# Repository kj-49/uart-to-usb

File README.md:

## UART to USB

A simple chip that converts up to 3 UART lines to USB. Only supports one-way transmission from UART to USB.

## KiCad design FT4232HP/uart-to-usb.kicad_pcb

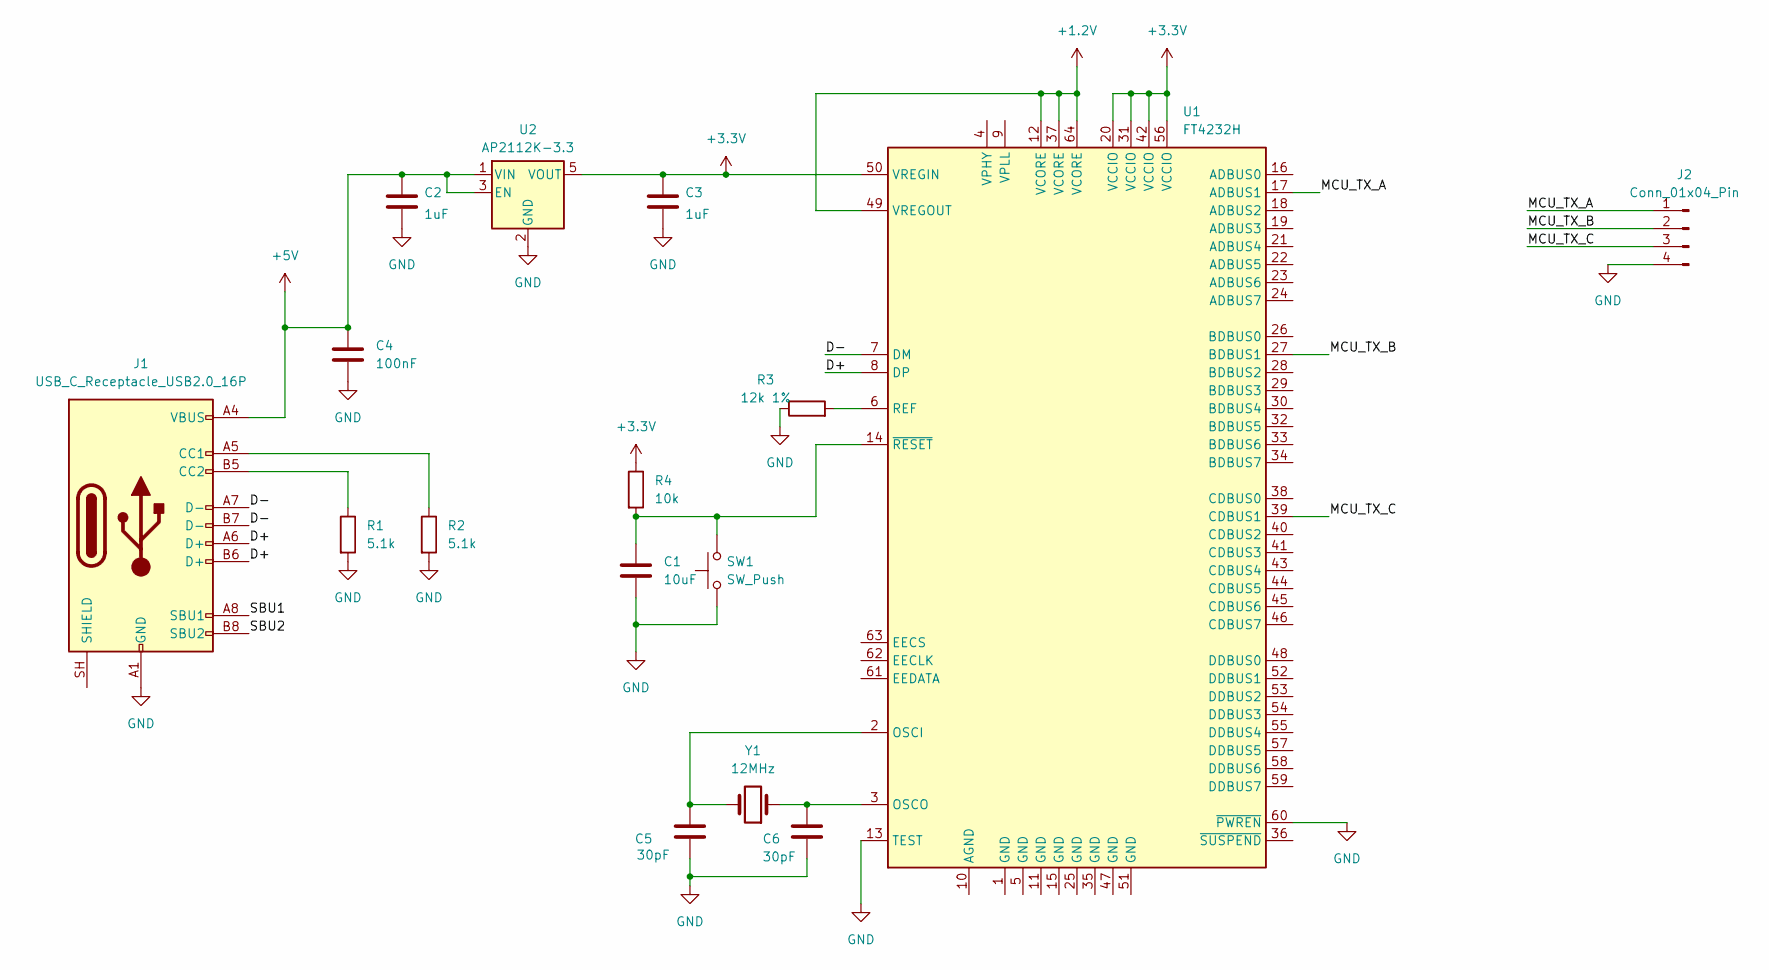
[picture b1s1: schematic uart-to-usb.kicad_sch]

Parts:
C1: 10uF; C_0805_2012Metric; LCSC C1713
C2, C3: 1uF; C_0805_2012Metric; LCSC C1712
C4: 100nF; C_0805_2012Metric; LCSC C1710
C5, C6: 30pF; C_0805_2012Metric; LCSC C43094
J1: USB_C_Receptacle_USB2.0_16P; USB_C_Receptacle_GCT_USB4105-xx-A_16P_TopMnt_Horizontal; LCSC C3020560
J2: Conn_01x04_Pin; JST_XH_S4B-XH-A_1x04_P2.50mm_Horizontal; LCSC C157925
R1, R2: 5.1k; R_0603_1608Metric; LCSC C23186
R3: 12k 1%; R_0805_2012Metric; LCSC C17444
R4: 10k; R_0805_2012Metric; LCSC C17414
SW1: SW_Push; SW_Push_SPST_NO_Alps_SKRK; LCSC C2939236
U1: FT4232H; QFN-64-1EP_9x9mm_P0.5mm_EP7.5x7.5mm; LCSC C8690
U2: AP2112K-3.3; SOT-23-5; LCSC C51118
Y1: 12MHz; Crystal_SMD_3225-4Pin_3.2x2.5mm; LCSC C9002

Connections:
+1.2V: U1.12 (VCORE), U1.37 (VCORE), U1.49 (VREGOUT), U1.64 (VCORE)
+3.3V: C3.1, R4.1, U1.20 (VCCIO), U1.31 (VCCIO), U1.42 (VCCIO), U1.50 (VREGIN), U1.56 (VCCIO), U2.5 (VOUT)
+5V: C2.1, C4.1, J1.A4 (VBUS), J1.A9 (VBUS), J1.B4 (VBUS), J1.B9 (VBUS), U2.1 (VIN), U2.3 (EN)
/D+: J1.A6 (D+), J1.B6 (D+), U1.8 (DP)
/D-: J1.A7 (D-), J1.B7 (D-), U1.7 (DM)
/MCU_TX_A: J2.1, U1.17 (ADBUS1)
/MCU_TX_B: J2.2, U1.27 (BDBUS1)
/MCU_TX_C: J2.3, U1.39 (CDBUS1)
/SBU1: J1.A8 (SBU1)
/SBU2: J1.B8 (SBU2)
GND: C1.2, C2.2, C3.2, C4.2, C5.2, C6.2, J1.A1 (GND), J1.A12 (GND), J1.B1 (GND), J1.B12 (GND), J2.4, R1.2, R2.2, R3.1, SW1.1, U1.13 (TEST), U1.60 (~PWREN), U2.2 (GND)
unnamed: J1.A5 (CC1), R2.1
unnamed: J1.B5 (CC2), R1.1
unnamed: C5.1, U1.2 (OSCI), Y1.2
unnamed: C6.1, U1.3 (OSCO), Y1.1
unnamed: R3.2, U1.6 (REF)
unnamed: C1.1, R4.2, SW1.2, U1.14 (~RESET)

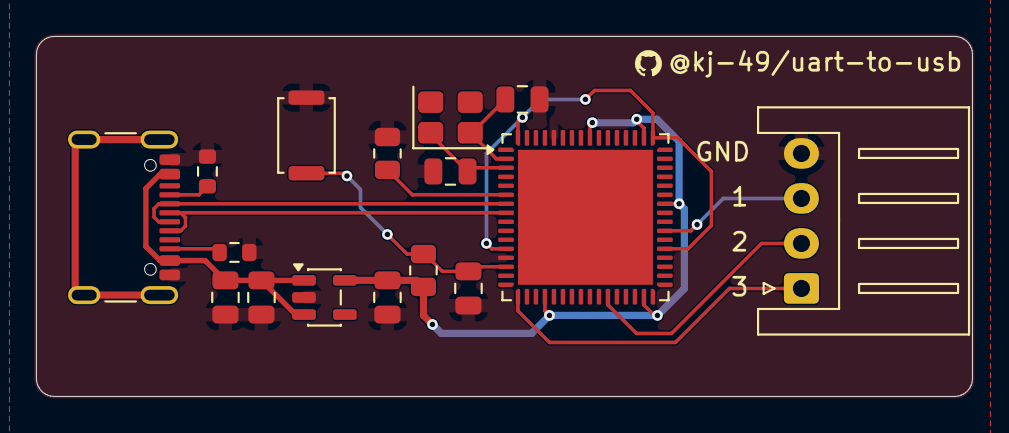
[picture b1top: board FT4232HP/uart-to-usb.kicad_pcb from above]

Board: 2 copper layers, 52.0 x 20.0 mm, 16 parts (0 on the bottom side), 15 nets.

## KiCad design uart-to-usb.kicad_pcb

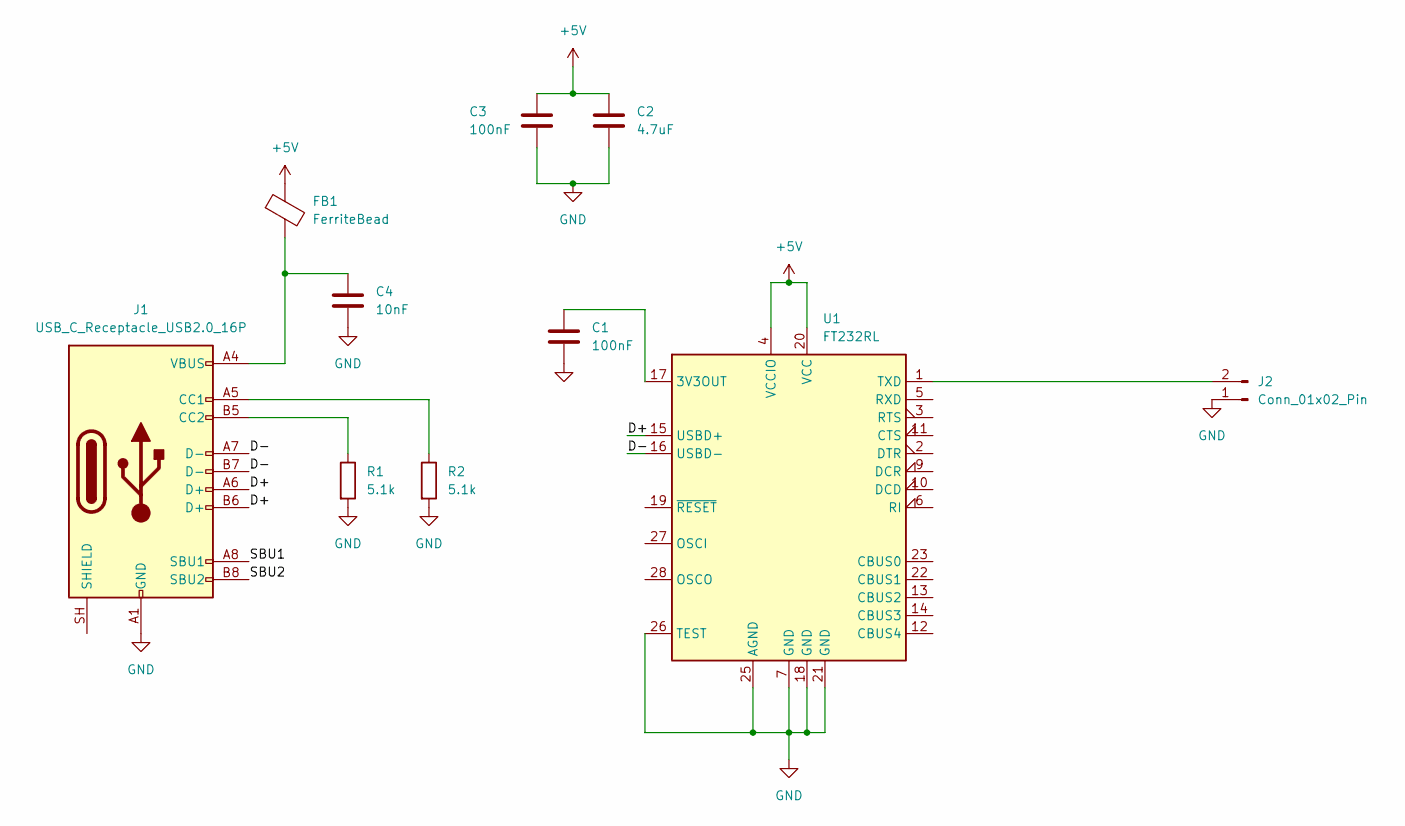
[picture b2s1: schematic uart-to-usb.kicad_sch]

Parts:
C1, C3: 100nF; C_0805_2012Metric; LCSC C1711
C2: 4.7uF; C_1206_3216Metric; LCSC C17936
C4: 10nF; C_0805_2012Metric; LCSC C1710
FB1: FerriteBead; L_0805_2012Metric; LCSC C1011
J1: USB_C_Receptacle_USB2.0_16P; USB_C_Receptacle_GCT_USB4105-xx-A_16P_TopMnt_Horizontal; LCSC C3020560
J2: Conn_01x02_Pin; JST_GH_SM02B-GHS-TB_1x02-1MP_P1.25mm_Horizontal; LCSC C189893
R1, R2: 5.1k; R_0603_1608Metric; LCSC C23186
U1: FT232RL; SSOP-28_5.3x10.2mm_P0.65mm; LCSC C8690

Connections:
+5V: C2.1, C3.1, FB1.1, U1.4 (VCCIO), U1.20 (VCC)
/D+: J1.A6 (D+), J1.B6 (D+), U1.15 (USBD+)
/D-: J1.A7 (D-), J1.B7 (D-), U1.16 (USBD-)
/SBU1: J1.A8 (SBU1)
/SBU2: J1.B8 (SBU2)
GND: C1.2, C2.2, C3.2, C4.2, J1.A1 (GND), J1.A12 (GND), J1.B1 (GND), J1.B12 (GND), J2.1, R1.2, R2.2, U1.7 (GND), U1.18 (GND), U1.21 (GND), U1.25 (AGND), U1.26 (TEST)
unnamed: C4.1, FB1.2, J1.A4 (VBUS), J1.A9 (VBUS), J1.B4 (VBUS), J1.B9 (VBUS)
unnamed: J1.A5 (CC1), R2.1
unnamed: J1.B5 (CC2), R1.1
unnamed: J2.2, U1.1 (TXD)
unnamed: C1.1, U1.17 (3V3OUT)

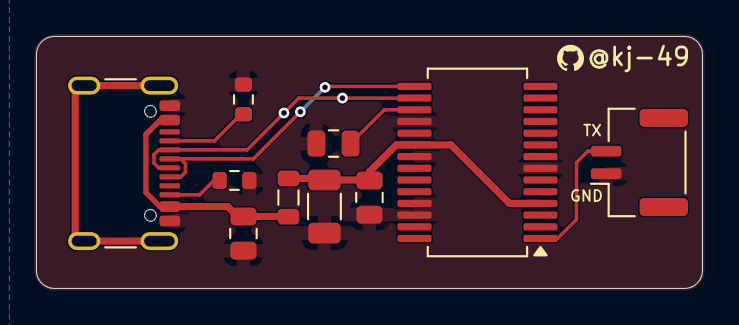
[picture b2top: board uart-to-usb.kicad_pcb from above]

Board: 2 copper layers, 37.0 x 14.0 mm, 10 parts (0 on the bottom side), 9 nets.

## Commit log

2026-05-28 Add gitignore
2026-05-28 Add project
2026-05-29 Setup basic schematic
2026-05-29 Assign footprints
2026-05-29 Start layout
2026-05-31 Initial PCB route
2026-05-31 Add profile
2026-05-31 Use single input connector
2026-05-31 Add render
2026-05-31 Add UART to USB PCB description to README
2026-05-31 Fix edge cut solder mask boundary
2026-05-31 Add part for BOM
2026-06-01 Add image to readme
2026-06-01 Fix usb-c alignment
2026-06-07 Setup FT4232 project
2026-06-20 Finish 4232 routing
2026-06-21 Add 3d model
2026-06-21 Use 4232 image
